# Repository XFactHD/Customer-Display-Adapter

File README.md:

# Customer Display Adapter

Simple adapter PCB to connect a Siemens Nixdorf BA63 Customer Display via USB.

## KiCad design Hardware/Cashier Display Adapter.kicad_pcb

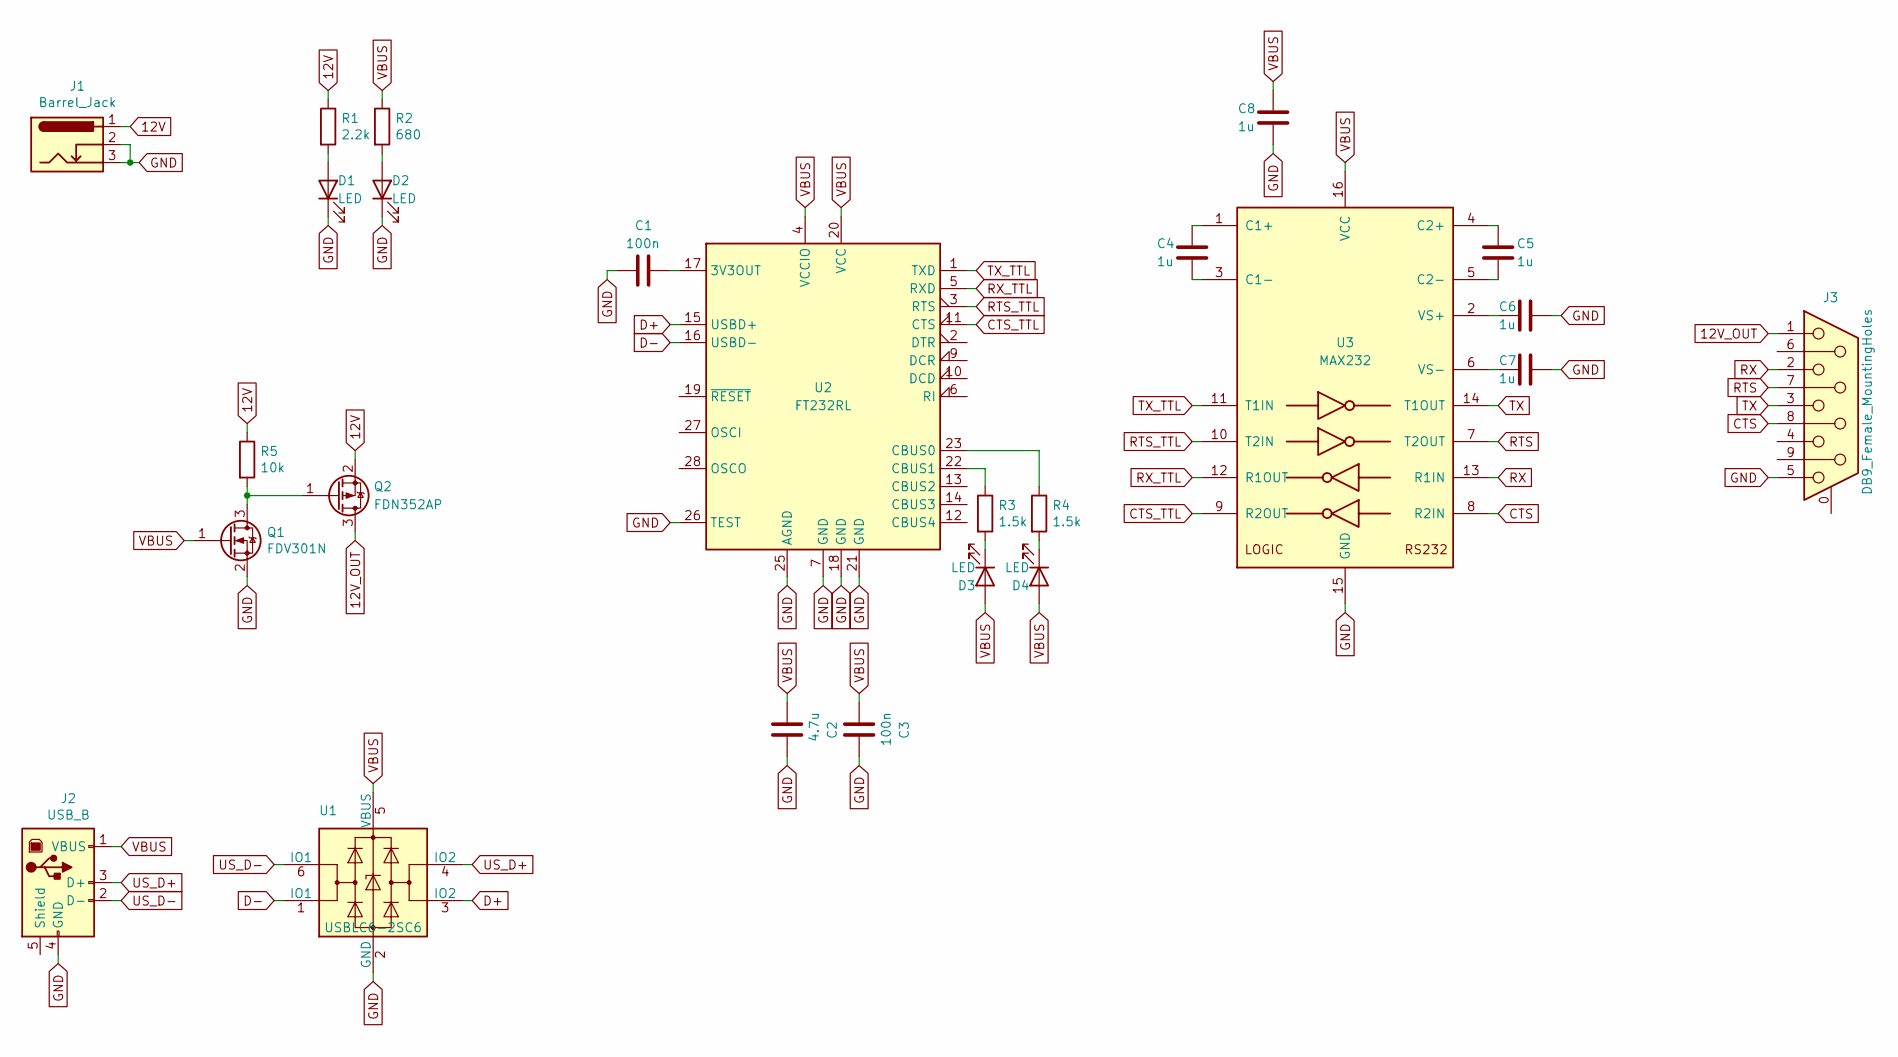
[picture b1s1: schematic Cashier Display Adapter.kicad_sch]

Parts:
C1, C3: 100n; C_0805
C2: 4.7u; C_0805
C4, C5, C6, C7, C8: 1u; C_0805
D1, D2, D3, D4: LED; LED_D1.8mm_W3.3mm_H2.4mm
J1: Barrel_Jack; dc_socket
J2: USB_B
J3: DB9_Female_MountingHoles; DB_9F
Q1: FDV301N; SOT-23
Q2: FDN352AP; SOT-23
R1: 2.2k; R_0805
R2: 680; R_0805
R3, R4: 1.5k; R_0805
R5: 10k; R_0805
U1: USBLC6-2SC6; SOT-23-6
U2: FT232RL; SSOP-28_5.3x10.2mm_Pitch0.65mm
U3: MAX232; SOIC-16W_7.5x10.3mm_Pitch1.27mm

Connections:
12V: J1.1, Q2.2 (S), R1.1, R5.1
12V_OUT: J3.1, Q2.3 (D)
CTS: J3.8, U3.8 (R2IN)
CTS_TTL: U2.11 (CTS), U3.9 (R2OUT)
D+: U1.3 (IO2), U2.15 (USBD+)
D-: U1.1 (IO1), U2.16 (USBD-)
GND: C1.2, C2.1, C3.1, C6.1, C7.1, C8.2, D1.1 (K), D2.1 (K), J1.2, J1.3, J2.4 (GND), J3.5, Q1.2 (S), U1.2 (GND), U2.7 (GND), U2.18 (GND), U2.21 (GND), U2.25 (AGND), U2.26 (TEST), U3.15 (GND)
unnamed: C1.1, U2.17 (3V3OUT)
unnamed: C4.1, U3.1 (C1+)
unnamed: C4.2, U3.3 (C1-)
unnamed: C5.1, U3.4 (C2+)
unnamed: C5.2, U3.5 (C2-)
unnamed: C6.2, U3.2 (VS+)
unnamed: C7.2, U3.6 (VS-)
unnamed: D1.2 (A), R1.2
unnamed: D2.2 (A), R2.2
unnamed: D3.1 (K), R3.2
unnamed: D4.1 (K), R4.2
unnamed: Q1.3 (D), Q2.1 (G), R5.2
unnamed: R3.1, U2.22 (CBUS1)
unnamed: R4.1, U2.23 (CBUS0)
RTS: J3.7, U3.7 (T2OUT)
RTS_TTL: U2.3 (RTS), U3.10 (T2IN)
RX: J3.2, U3.13 (R1IN)
RX_TTL: U2.5 (RXD), U3.12 (R1OUT)
TX: J3.3, U3.14 (T1OUT)
TX_TTL: U2.1 (TXD), U3.11 (T1IN)
US_D+: J2.3 (D+), U1.4 (IO2)
US_D-: J2.2 (D-), U1.6 (IO1)
VBUS: C2.2, C3.2, C8.1, D3.2 (A), D4.2 (A), J2.1 (VBUS), Q1.1 (G), R2.1, U1.5 (VBUS), U2.4 (VCCIO), U2.20 (VCC), U3.16 (VCC)

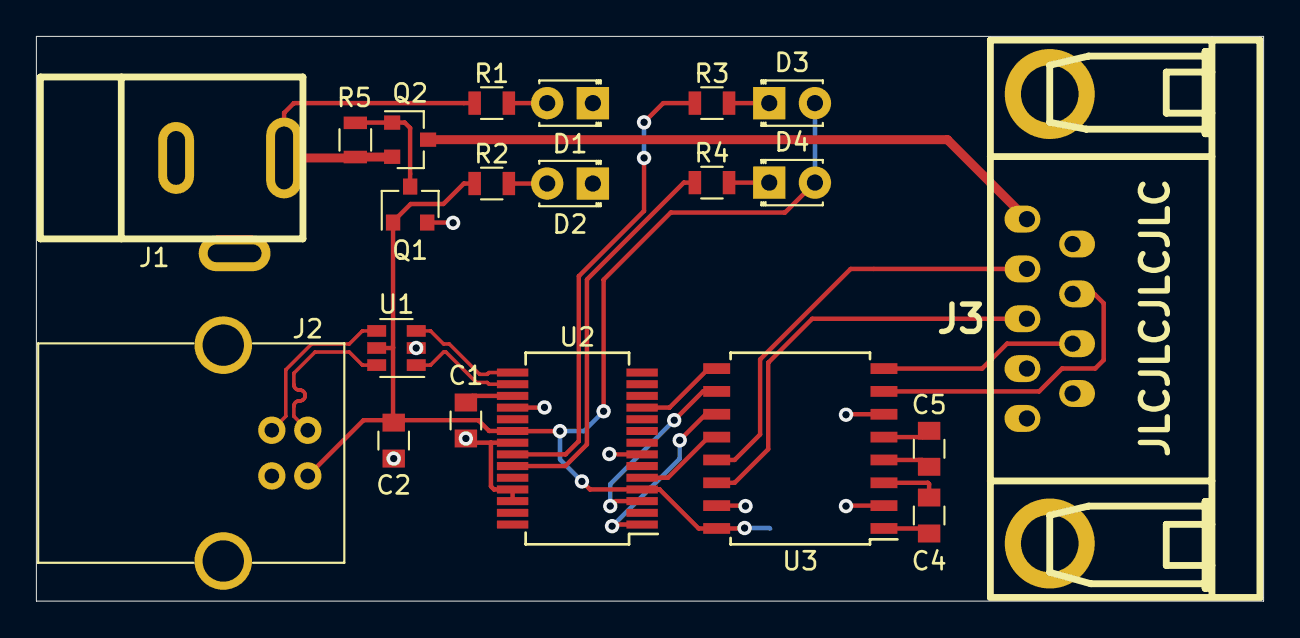
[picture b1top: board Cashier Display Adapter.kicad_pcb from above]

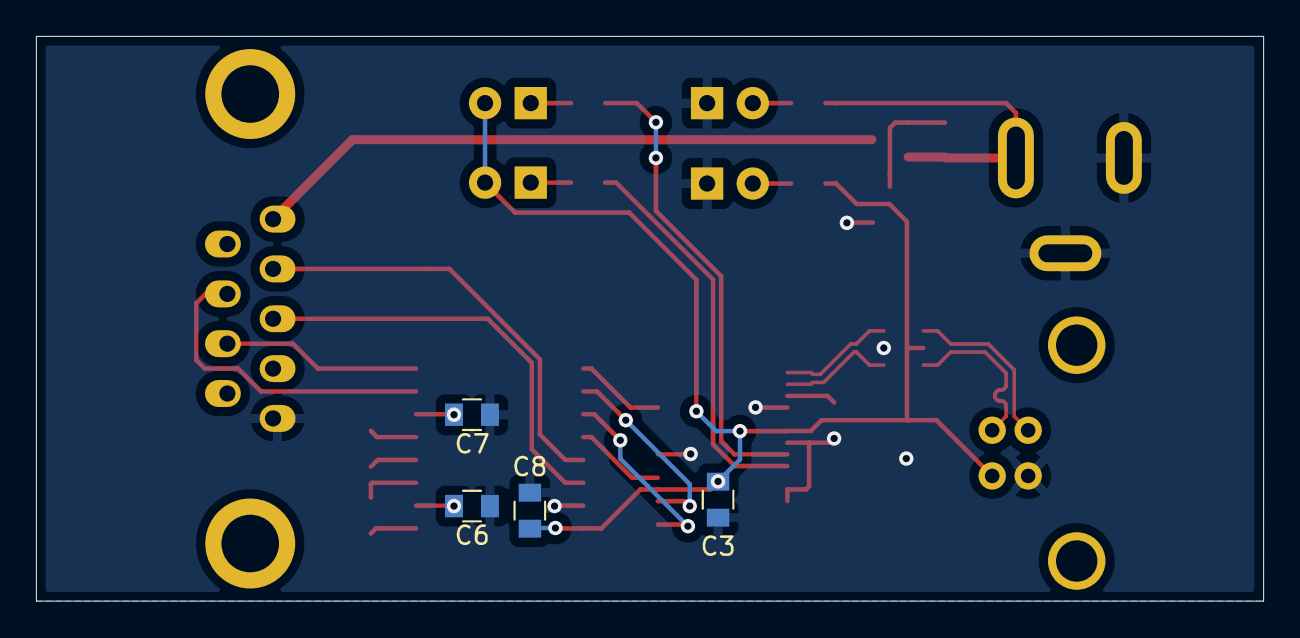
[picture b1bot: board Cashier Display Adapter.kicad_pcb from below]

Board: 2 copper layers, 68.2 x 31.4 mm, 25 parts (4 on the bottom side), 30 nets.
